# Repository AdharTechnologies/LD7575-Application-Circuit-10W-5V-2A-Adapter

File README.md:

# Reference Application Circuit 10W (5V/2A) Adapter 

Circuit has been designed based on LD7575 datasheet

#NOTE

1. Circuit has not been tested
2. Components are not accurate

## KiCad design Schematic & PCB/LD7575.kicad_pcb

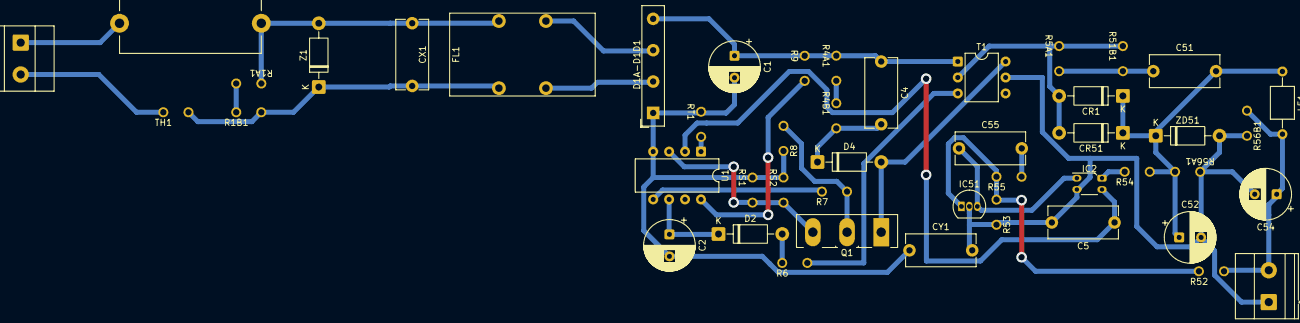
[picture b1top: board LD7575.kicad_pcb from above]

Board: 2 copper layers, 45 parts (0 on the bottom side), 28 nets.

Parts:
C1: 22μF, 400V; CP_Radial_D8.0mm_P3.50mm
C2: 22μF, 50V; CP_Radial_D8.0mm_P3.50mm
C4: 1000pF, 1000V; C_Disc_D11.0mm_W5.0mm_P10.00mm
C5: 0.01uF. 16V; C_Disc_D11.0mm_W5.0mm_P10.00mm
C51: 1000pF. 50V; C_Disc_D11.0mm_W5.0mm_P10.00mm
C52: 1000μF, 10V; CP_Radial_D8.0mm_P3.50mm
C54: 470μF, 10V; CP_Radial_D8.0mm_P3.50mm
C55: 0.0221uF. 16V; C_Disc_D11.0mm_W5.0mm_P10.00mm
CR1, CR51: SB540; D_DO-41_SOD81_P10.16mm_Horizontal
CX1: 0.1uF; C_Disc_D11.0mm_W5.0mm_P10.00mm
CY1: 2200pF; C_Disc_D11.0mm_W5.0mm_P10.00mm
D1A-D1D1: 1N4007; Diode_Bridge_19.0x3.5x10.0mm_P5.0mm
D2: PS102R; D_DO-41_SOD81_P10.16mm_Horizontal
D4: 1N4007; D_DO-41_SOD81_P10.16mm_Horizontal
F1: Fuse 250V, 1A; Fuseholder_Cylinder-5x20mm_Stelvio-Kontek_PTF78_Horizontal_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
FL1: 20mH; L_CommonMode_Wuerth_WE-CMB-M
IC2: El817B; OnSemi_CASE100AQ
IC51: TL431LP; TO-92_Inline
L51: 2.7uH; L_Axial_L5.0mm_D3.6mm_P10.00mm_Horizontal_Murata_BL01RN1A2A2
Q1: 2N60B; TO-247-3_Vertical
R1A1, R1B1: R_Small_US; resistor
R4A1, R4B1: 39K; resistor
R5A1, R51B1, R54: 100; resistor
R6: 2.2; resistor
R7: 10; resistor
R8, R9: 10K; resistor
R52, R53: 2.49K; resistor
R55: 1K; resistor
R56A1: 2.7K; resistor
R56B1: resistor
RS1, RS2: 2.7; resistor
RT1: 100K; resistor
T1: PA0264NL; DIP-6_W7.62mm
TH1: Thermistor_NTC; resistor
U1: LD7575; CERDIP-8_W7.62mm_SideBrazed
Z1: TVS_Diode; D_DO-41_SOD81_P10.16mm_Horizontal
ZD51: 6V2C; D_DO-41_SOD81_P10.16mm_Horizontal

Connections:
AUX XMER: R6.2, T1.3
Compensator INPUT: C5.1, IC2.4, U1.2 (COMP)
GNDPWR: C1.2, C2.2, CY1.1, D1A-D1D1.1 (-), R8.1, RS1.1, RS2.1, RT1.1, U1.4 (GND)
GNDREF: C5.2, C52.2, C54.2, CY1.2, IC2.3, IC51.2 (A), R53.1, R56A1.1, R56B1.1, T1.5, ZD51.2 (A)
unnamed: C51.1, R5A1.2, R51B1.2
unnamed: C55.2, R55.2
unnamed: CR1.2 (A), CR51.2 (A), R5A1.1, R51B1.1, T1.2
unnamed: C51.2, C52.1, CR1.1 (K), CR51.1 (K), L51.1, R54.2, R56A1.2, ZD51.1 (K)
unnamed: C1.1, C4.1, D1A-D1D1.4 (+), R4A1.1, R9.1, T1.1
unnamed: D1A-D1D1.2, FL1.3
unnamed: D1A-D1D1.3, FL1.4
unnamed: D2.2 (A), R6.1
unnamed: C2.1, D2.1 (K), U1.6 (VCC)
unnamed: D4.2 (A), Q1.1 (D), T1.6
unnamed: C4.2, D4.1 (K), R4B1.2
unnamed: IC2.1, R54.1
unnamed: C55.1, IC2.2, IC51.3 (K)
unnamed: IC51.1 (REF), R52.1, R53.2, R55.1
unnamed: C54.1, L51.2, R52.2, R56B1.2
unnamed: Q1.2 (G), R7.2, R8.2
unnamed: Q1.3 (S), RS1.2, RS2.2, U1.3 (CS)
unnamed: R1A1.2, R1B1.1
unnamed: R4A1.2, R4B1.1
unnamed: R9.2, U1.8 (HV)
unnamed: R7.1, U1.5 (OUT)
unnamed: RT1.2, U1.1 (RT)
unnamed: CX1.2, FL1.1, R1B1.2, TH1.2, Z1.1 (A1)
unnamed: CX1.1, F1.2, FL1.2, R1A1.1, Z1.2 (A2)

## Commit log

2026-03-11 LICENSE
